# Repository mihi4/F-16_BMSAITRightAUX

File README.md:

# !!! ATTENTION !!!!
## I don't use BMSAIT anymore, so this repository is quite outdated and never got into my sim as it is

# BMSAIT Right Aux Controller
* Microcontroller: Arduino Nano

## Hardware controlled
- PFD
- CAUTION PANEL
- COMPASS
- FUEL QTY Gauge
- HYD PRESS Gauges
- EPU FUEL Gauge
- CABIN PRESS Gauge
- ~~(LIQUID FUEL Gauge)~~
- SIM1 Panel (??? 3 LEDs of MM5451 available)
## Pinmapping
* PFD: 
  * Serial Display  
    (Old DED, 2 pins, softwareSerial) D2,D3
* CAUTION PANEL:
  * 1 MM5451  
    (2 pins) D4,D5
* HYD PRESS:
  * 2 Servos  
    (2 pins) D6,D7
* FUEL QTY:
  * 2 servos  
    (2 pins) D8,D9
  * MAX7219 5 digit 7seg display  
    (3 pins) D10,D11,D12
* AX1201728SG (7 pins), D13-A5
  * COMPASS: 1 X27  
    (2 pins)
  * CABIN PRESS: 1 X27  
    (2 pins)
  * EPU FUEL: 1 X27  
    (2 pins)  
* Input for compass seroizing sensor (1 pin) A6  
* Input for compass seroizing button (1 pin) A7

## !!! Use those files at your own risk !!!

All the files are free to use under the GNUGPLv3

If you find those files useful and would like to support me with an icecream, coffee or pizza, you can use paypal.me to do so ;)  
[Paypal.me](https://paypal.me/MichiHirczy)

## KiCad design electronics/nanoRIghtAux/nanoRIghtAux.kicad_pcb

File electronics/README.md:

# KiCAD files and other files related to electronics hardware

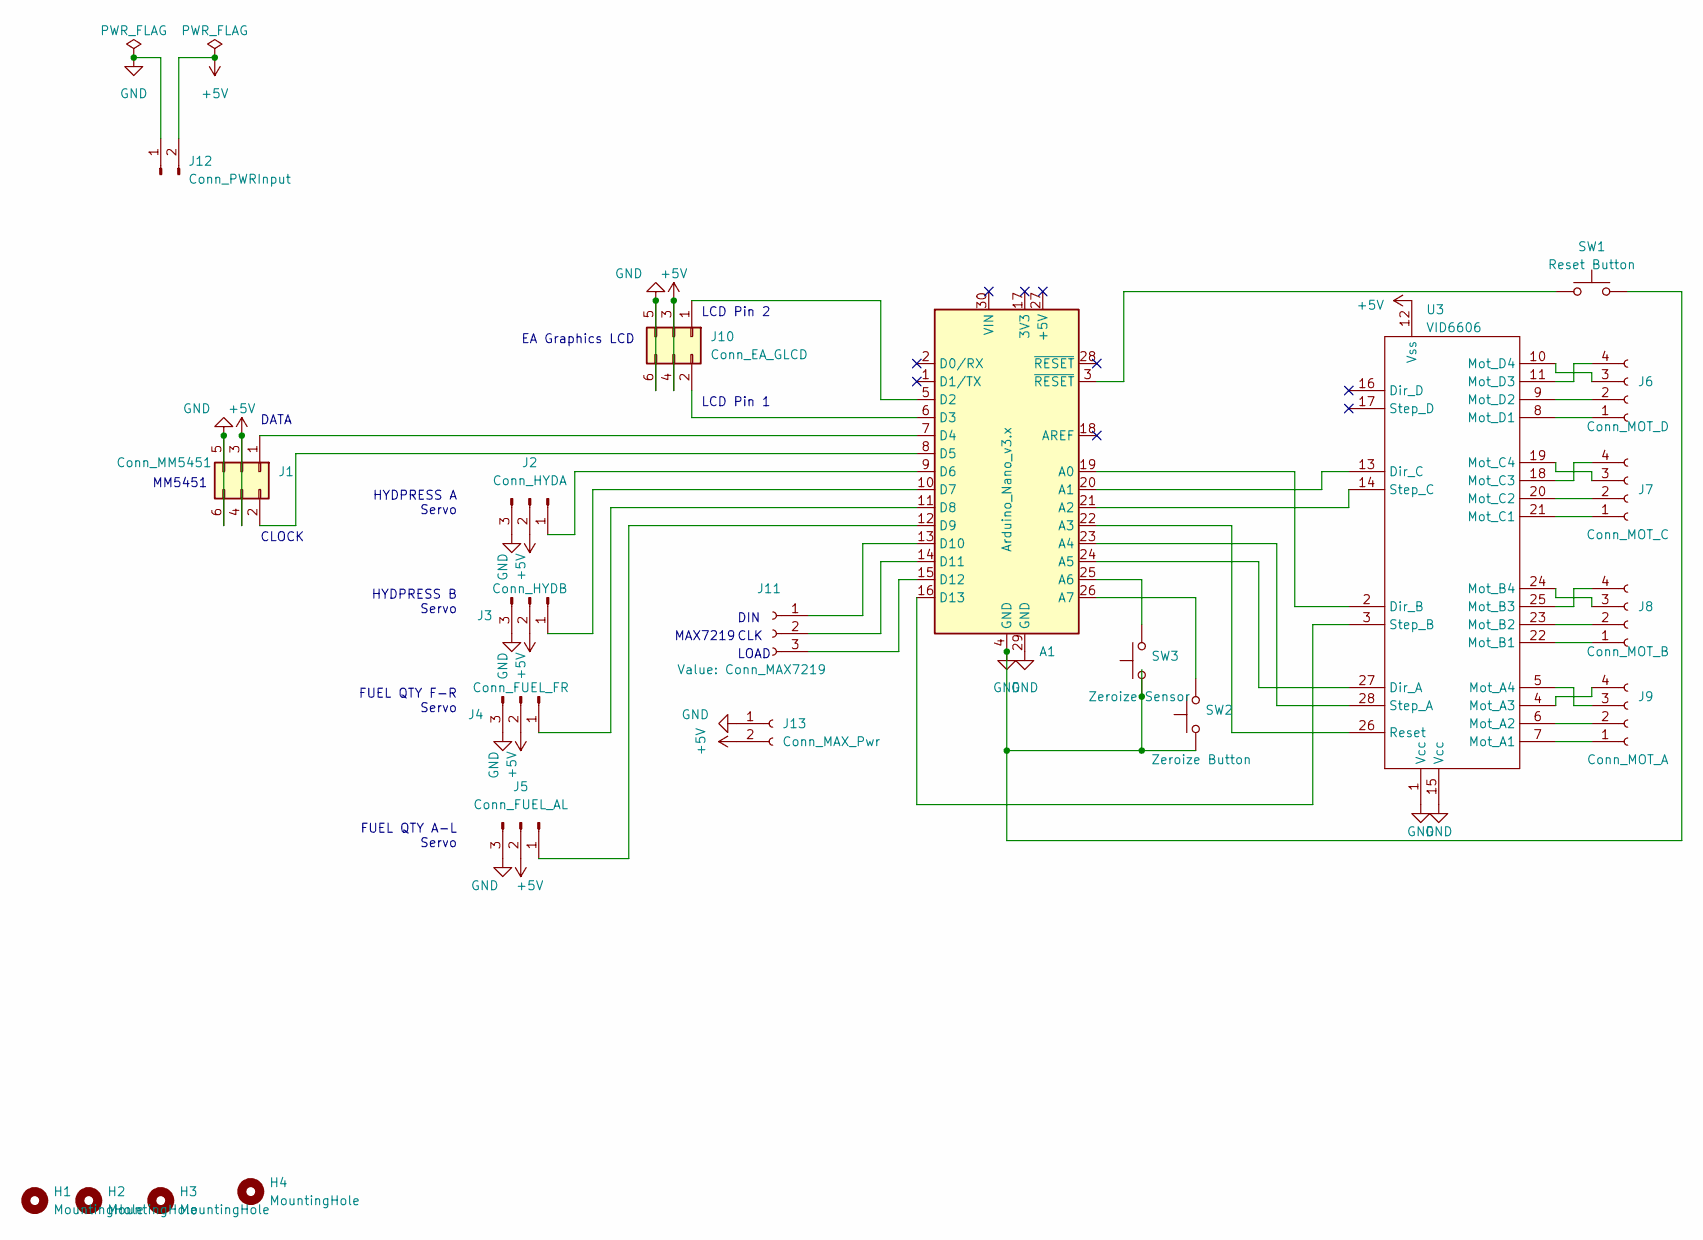
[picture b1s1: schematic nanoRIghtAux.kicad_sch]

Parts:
A1: Arduino_Nano_v3.x; Arduino_Nano
H1, H2, H3, H4: MountingHole; MountingHole_3.5mm
J1: Conn_MM5451; PinHeader_2x03_P2.54mm_Vertical
J2: Conn_HYDA; PinHeader_1x03_P2.54mm_Vertical
J3: Conn_HYDB; PinHeader_1x03_P2.54mm_Vertical
J4: Conn_FUEL_FR; PinHeader_1x03_P2.54mm_Vertical
J5: Conn_FUEL_AL; PinHeader_1x03_P2.54mm_Vertical
J6: Conn_MOT_D; PinHeader_1x04_P2.54mm_Vertical
J7: Conn_MOT_C; PinHeader_1x04_P2.54mm_Vertical
J8: Conn_MOT_B; PinHeader_1x04_P2.54mm_Vertical
J9: Conn_MOT_A; PinHeader_1x04_P2.54mm_Vertical
J10: Conn_EA_GLCD; PinHeader_2x03_P2.54mm_Vertical
J11: Conn_MAX7219; PinSocket_1x03_P2.54mm_Vertical
J12: Conn_PWRInput; PinHeader_1x02_P2.54mm_Vertical
J13: Conn_MAX_Pwr; PinSocket_1x02_P2.54mm_Vertical
SW1: Reset Button; PinHeader_1x02_P2.54mm_Vertical
SW2: Zeroize Button; PinHeader_1x02_P2.54mm_Vertical
SW3: Zeroize Sensor; PinHeader_1x02_P2.54mm_Vertical
U3: VID6606; DIP-28_W15.24mm

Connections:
+5V: J1.3, J1.4, J2.2, J3.2, J4.2, J5.2, J10.3, J10.4, J12.2, J13.2, U3.12 (Vss)
GND: A1.4 (GND), A1.29 (GND), J1.5, J1.6, J2.3, J3.3, J4.3, J5.3, J10.5, J10.6, J12.1, J13.1, SW1.2, SW2.1, SW3.1, U3.1 (Vcc), U3.15 (Vcc)
unnamed: A1.19 (A0), U3.2 (Dir_B)
unnamed: A1.20 (A1), U3.13 (Dir_C)
unnamed: A1.21 (A2), U3.14 (Step_C)
unnamed: A1.22 (A3), U3.26 (Reset)
unnamed: A1.23 (A4), U3.28 (Step_A)
unnamed: A1.24 (A5), U3.27 (Dir_A)
unnamed: A1.25 (A6), SW3.2
unnamed: A1.26 (A7), SW2.2
unnamed: A1.5 (D2), J10.1
unnamed: A1.6 (D3), J10.2
unnamed: A1.7 (D4), J1.1
unnamed: A1.8 (D5), J1.2
unnamed: A1.9 (D6), J2.1
unnamed: A1.10 (D7), J3.1
unnamed: A1.11 (D8), J4.1
unnamed: A1.12 (D9), J5.1
unnamed: A1.13 (D10), J11.1
unnamed: A1.14 (D11), J11.2
unnamed: A1.15 (D12), J11.3
unnamed: A1.16 (D13), U3.3 (Step_B)
unnamed: A1.3 (~RESET), SW1.1
unnamed: J6.1, U3.8 (Mot_D1)
unnamed: J6.2, U3.9 (Mot_D2)
unnamed: J6.3, U3.10 (Mot_D4)
unnamed: J6.4, U3.11 (Mot_D3)
unnamed: J7.1, U3.21 (Mot_C1)
unnamed: J7.2, U3.20 (Mot_C2)
unnamed: J7.3, U3.19 (Mot_C4)
unnamed: J7.4, U3.18 (Mot_C3)
unnamed: J8.1, U3.22 (Mot_B1)
unnamed: J8.2, U3.23 (Mot_B2)
unnamed: J8.3, U3.24 (Mot_B4)
unnamed: J8.4, U3.25 (Mot_B3)
unnamed: J9.1, U3.7 (Mot_A1)
unnamed: J9.2, U3.6 (Mot_A2)
unnamed: J9.3, U3.5 (Mot_A4)
unnamed: J9.4, U3.4 (Mot_A3)

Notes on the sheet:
LOAD
HYDPRESS A Servo
HYDPRESS B Servo
FUEL QTY F-R Servo
CLK
CLOCK
MAX7219
FUEL QTY A-L Servo
DATA
LCD Pin 2
LCD Pin 1
EA Graphics LCD
MM5451
DIN

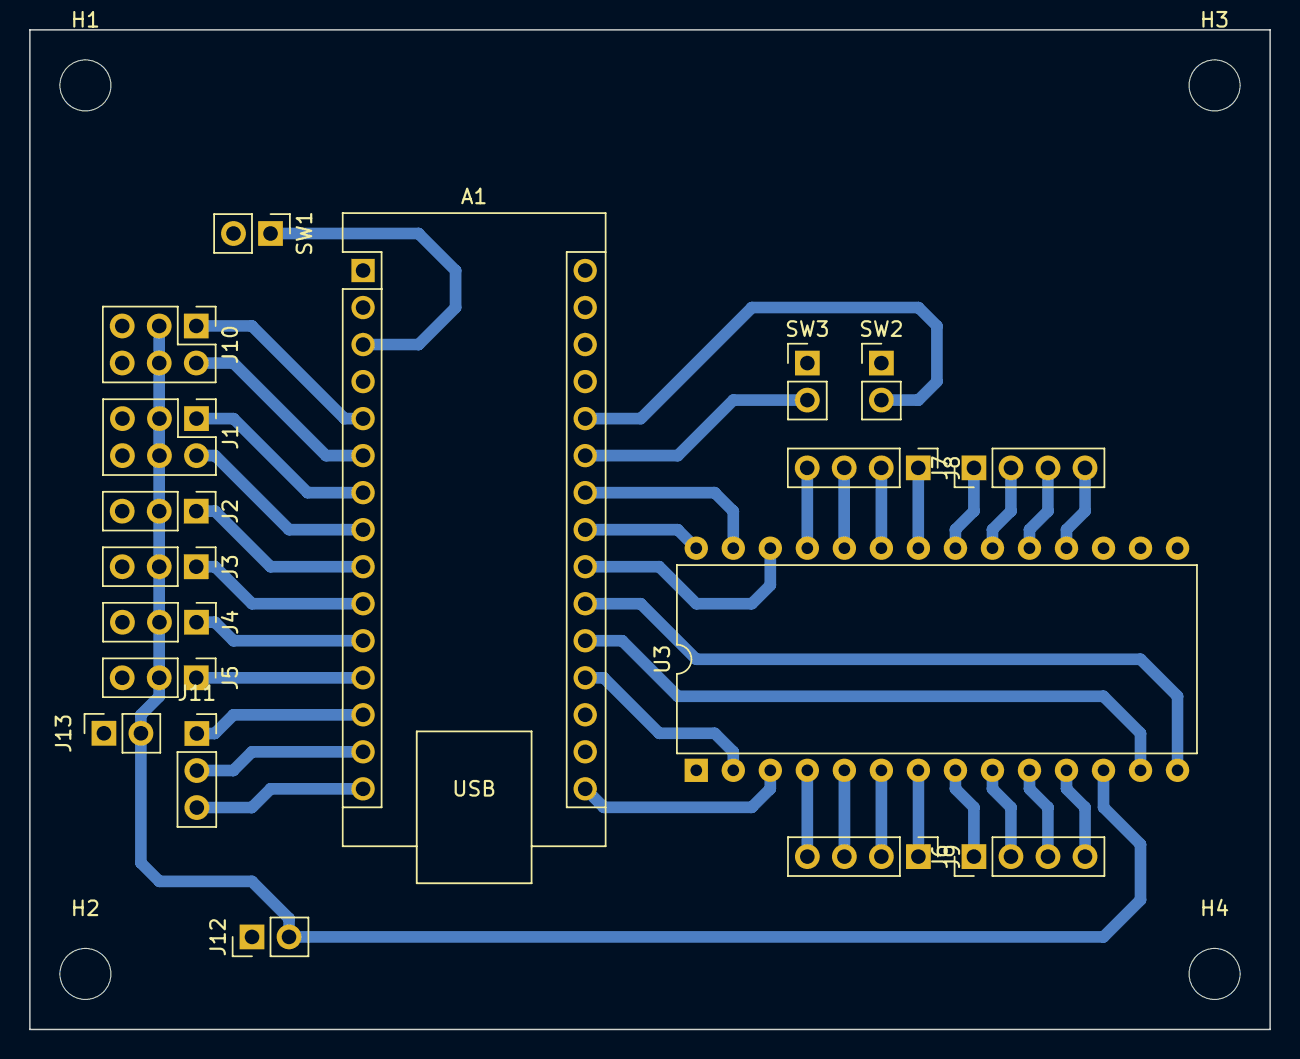
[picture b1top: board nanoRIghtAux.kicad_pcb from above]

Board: 2 copper layers, 85.1 x 68.6 mm, 22 parts (0 on the bottom side), 39 nets.

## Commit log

2023-05-21 changed directory names of BMSAIT controllers
2023-05-23 Update BMSAIT_LED_MM5451.h, BMSAIT_RightAuxController.ino, and 13 more files...
2023-05-26 win/linux encoding(?)
2023-06-06 added builtin LED for some tests
2023-06-09 added builtin led fo status display atm
2023-06-14 started adding connectors
2023-06-14 removed servos, connectors only
2023-06-14 Update fp-info-cache
2023-06-14 exchanged all parts with connectors
2023-06-14 connectors renamed
2023-06-14 changed 2x03 connector type
2023-06-14 PCB edit started
2023-06-14 PWR input pinheader added, MAX7219_PWR pinheader added, PCB routing changed
2023-06-14 first routing of TH components done.
2023-06-14 routing cleanup of TH components
2023-06-14 first gerber/echelon outputs
2023-06-14 Flatcam Project started
2023-06-14 mountingholes addes
2023-06-15 changed footprint of AX12 to DIP28
2023-06-15 changed pin assignments for AX12 to facilitate routing
2023-06-15 new routing started, 12mm hole for placint GX12 connector added
2023-06-15 structure cleanup
2023-06-15 text on frontside added
2023-06-15 more routing added
2023-06-15 routing done
2023-06-15 first routing finished, exported Gerbers/Drillfiles
2023-06-15 updated pcb, added 12mm hole to user drawings layer
2023-06-19 Update nanoRIghtAux-B_Cu.gbr, nanoRIghtAux-Edge_Cuts.gbr, and 6 more files...
2023-06-19 first fully completed pcb workflow
2023-06-19 layer changes
2023-06-20 new project, fixed missing z depth in isolation routings also front text is now iso-routed
2023-06-20 changed Z travel height
